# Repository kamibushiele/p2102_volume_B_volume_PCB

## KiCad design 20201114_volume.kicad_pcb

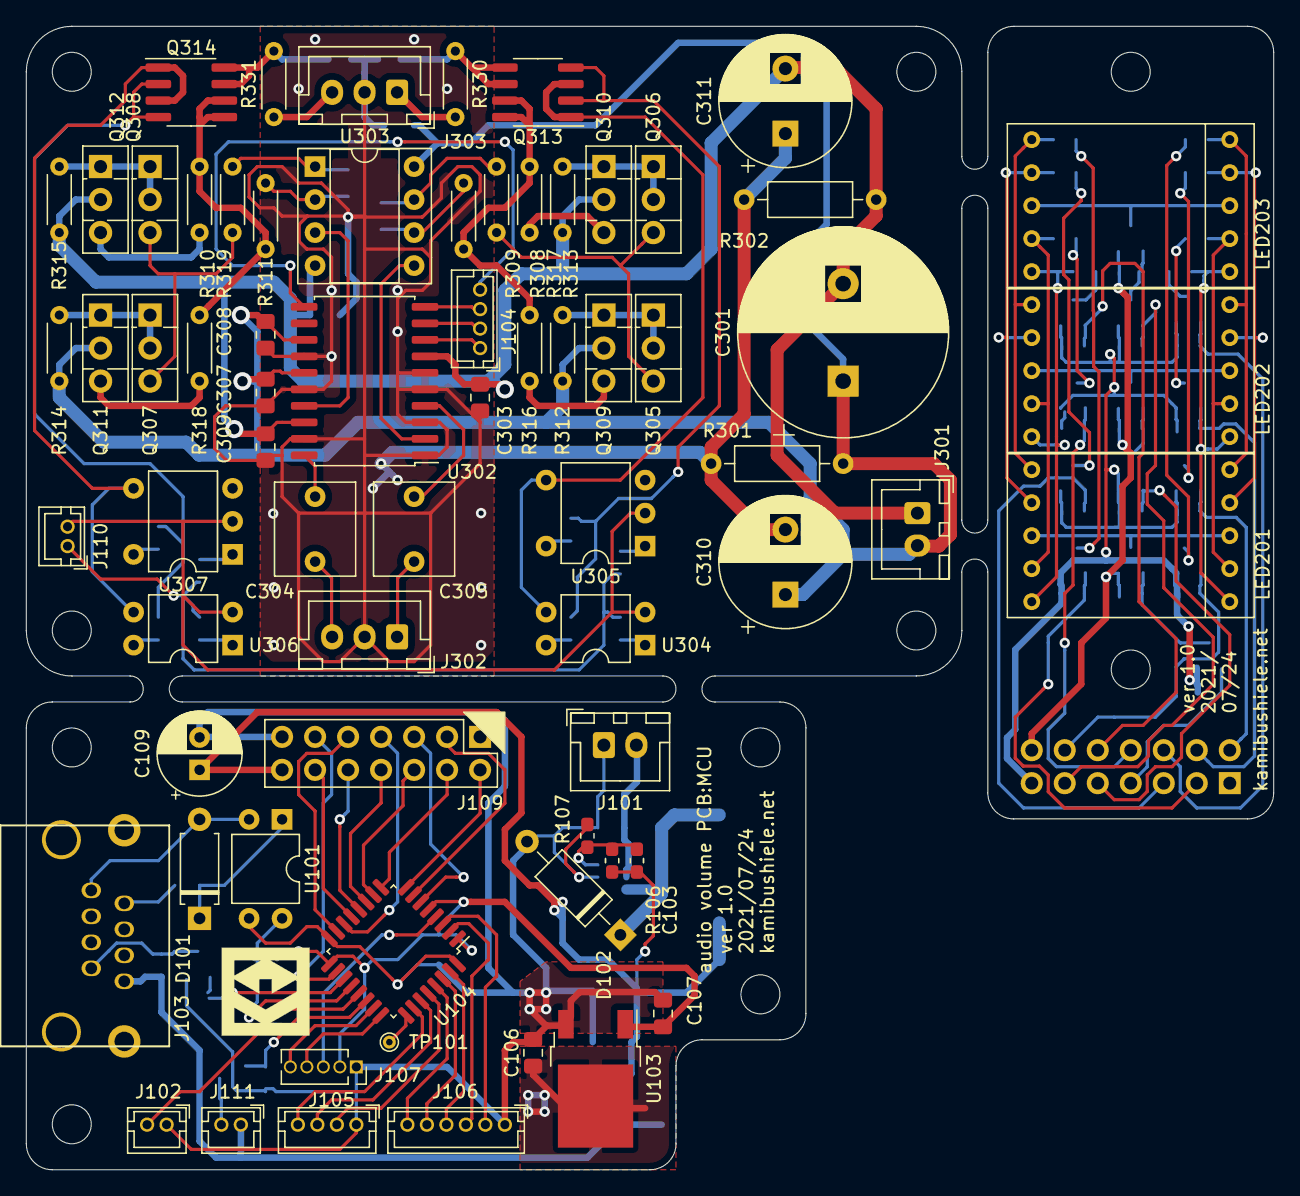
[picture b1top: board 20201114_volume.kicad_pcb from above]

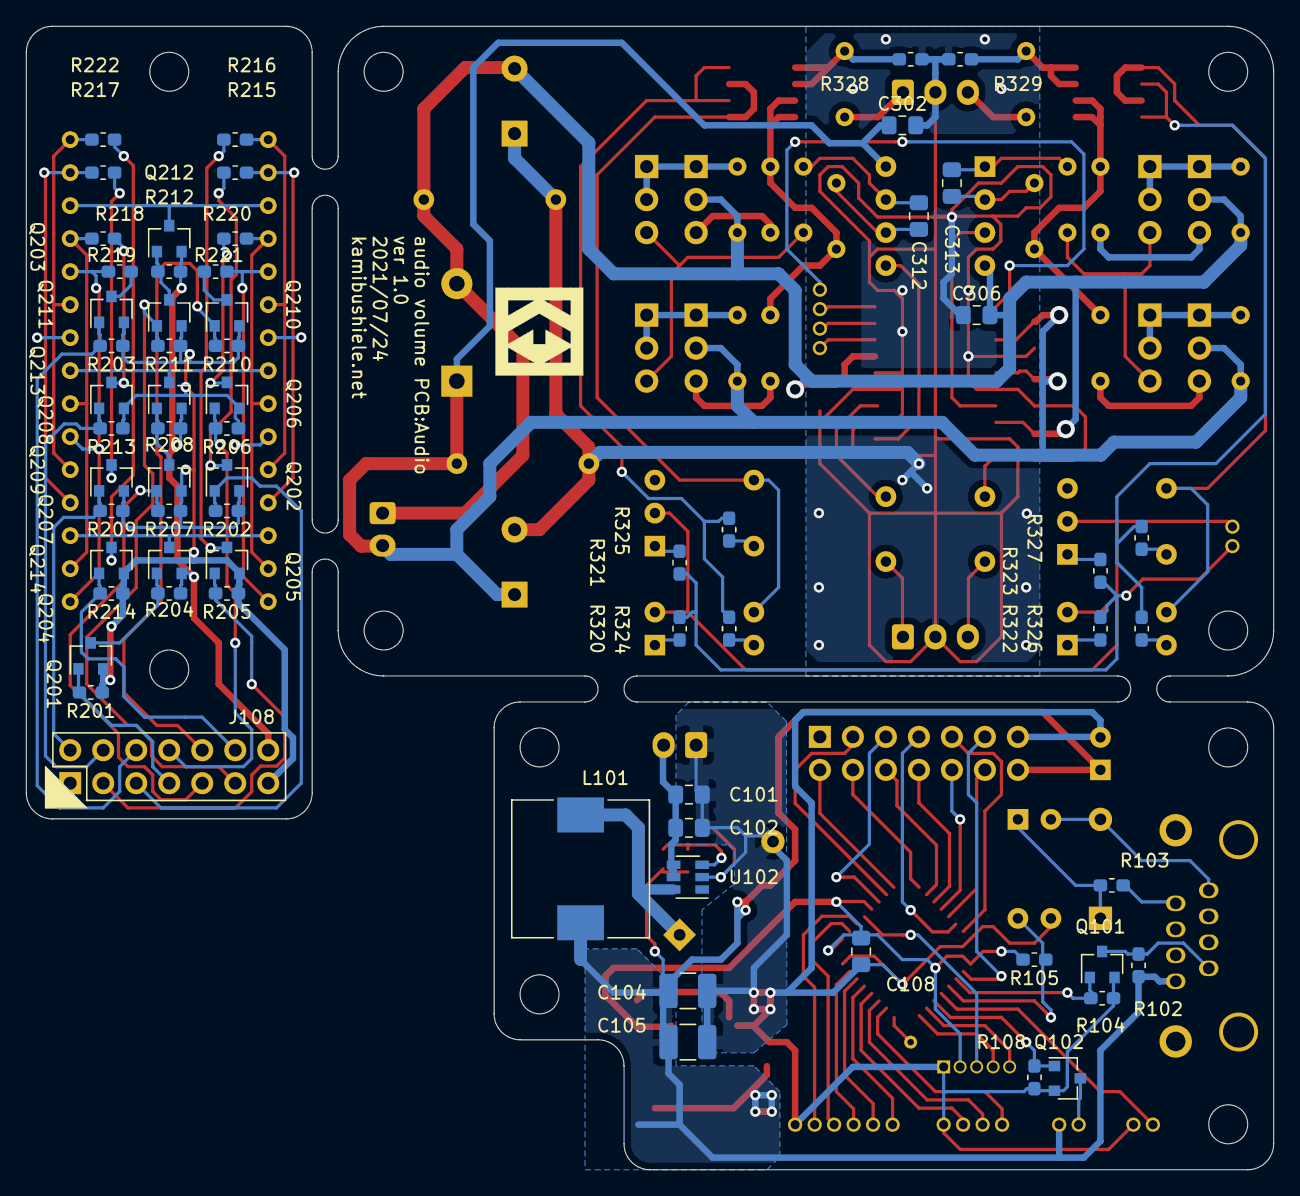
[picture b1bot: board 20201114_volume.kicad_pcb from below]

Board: 2 copper layers, 96.0 x 88.0 mm, 144 parts (65 on the bottom side), 120 nets.

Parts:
C101: 2.2uF 25V; C_0805_2012Metric_Pad1.15x1.40mm_HandSolder
C102: 2.2uF 25V NC; C_0805_2012Metric_Pad1.15x1.40mm_HandSolder
C103: 1000pF 50V; C_0603_1608Metric_Pad1.05x0.95mm_HandSolder
C104: 47uF 16V; C_1210_3225Metric_Pad1.42x2.65mm_HandSolder
C105: 47uF 16V NC; C_1210_3225Metric_Pad1.42x2.65mm_HandSolder
C106, C107, C108, C303, C307, C308, C309: 0.1u; C_0805_2012Metric_Pad1.15x1.40mm_HandSolder
C109: NC 47u; CP_Radial_D6.3mm_P2.50mm
C301: 470u; CP_Radial_D16.0mm_P7.50mm
C302, C306, C312, C313: NC; C_0805_2012Metric_Pad1.15x1.40mm_HandSolder
C304, C305: 1u; C_Rect_L7.0mm_W6.0mm_P5.00mm
C310, C311: 470u; CP_Radial_D10.0mm_P5.00mm
D101: D; D_A-405_P7.62mm_Horizontal
D102: SB240LES; D_A-405_P10.16mm_Horizontal
H101, H102, H103, H104, H201, H202, H301, H302, H303, H304: mounting_hole; M3-drillHole_6mm_nosilk_nopad
J101, J301: POWER; JST_XH_B2B-XH-A_1x02_P2.50mm_Vertical
J102: POWER_SW_DETECT; JST_ZH_B2B-ZR_1x02_P1.50mm_Vertical
J103: 8P8C_Shielded; 7810-8P8C
J104: AudiotoMCU; JST_ZH_B4B-ZR_1x04_P1.50mm_Vertical
J105: MCUtoAudio; JST_ZH_B4B-ZR_1x04_P1.50mm_Vertical
J106: ENC; JST_ZH_B6B-ZR_1x06_P1.50mm_Vertical
J107: SWD; PinSocket_1x05_P1.27mm_Vertical
J108: LEDtoMCU; PinHeader_2x07_P2.54mm_Vertical
J109: MCUtoLED; PinHeader_2x07_P2.54mm_Vertical
J110, J111: Mute; JST_ZH_B2B-ZR_1x02_P1.50mm_Vertical
J302, J303: IN; JST_XH_B3B-XH-A_1x03_P2.50mm_Vertical
L101: 22u; L_10.4x10.4_H4.8
LED201, LED202, LED203: OSL10564-IYG; OSL10564
Q101, Q102, Q201, Q202, Q203, Q205, Q206, Q207, Q209, Q210, Q211, Q213, Q214: 2N7002K; SOT-23
Q204, Q208, Q212: IRLML2246TRPbF; SOT-23
Q305, Q307, Q309, Q311: TTC004B; TO-126-3_Vertical
Q306, Q308, Q310, Q312: TTA004B; TO-126-3_Vertical
Q313, Q314: [mu]PA2753GR; SOP-8_3.76x4.96mm_P1.27mm
R102: 10k_NC; R_0603_1608Metric_Pad1.05x0.95mm_HandSolder
R103, R215, R216, R217, R218, R219, R220, R221, R222, R324, R325, R326, R327: 220; R_0603_1608Metric_Pad1.05x0.95mm_HandSolder
R104, R108, R201, R202, R203, R205, R206, R207, R209, R210, R211, R213, R214: 100k; R_0603_1608Metric_Pad1.05x0.95mm_HandSolder
R105: 100k_NC; R_0603_1608Metric_Pad1.05x0.95mm_HandSolder
R106: 3k; R_0603_1608Metric_Pad1.05x0.95mm_HandSolder
R107, R320, R322: 1k; R_0603_1608Metric_Pad1.05x0.95mm_HandSolder
R204, R208, R212, R328, R329: 10k; R_0603_1608Metric_Pad1.05x0.95mm_HandSolder
R301, R302: 1k; R_Axial_DIN0207_L6.3mm_D2.5mm_P10.16mm_Horizontal
R308, R310, R330, R331: 10; R_Axial_DIN0204_L3.6mm_D1.6mm_P5.08mm_Horizontal
R309, R311: 0; R_Axial_DIN0204_L3.6mm_D1.6mm_P5.08mm_Horizontal
R312, R313, R314, R315: 1.2k; R_Axial_DIN0204_L3.6mm_D1.6mm_P5.08mm_Horizontal
R316, R317, R318, R319: 5; R_Axial_DIN0204_L3.6mm_D1.6mm_P5.08mm_Horizontal
R321, R323: 500; R_0603_1608Metric_Pad1.05x0.95mm_HandSolder
TP101: TestPoint; TestPoint_THTPad_D1.0mm_Drill0.5mm
U101: TLP785; DIP-4_W7.62mm
U102: NJW1933-T; SOT-23-6
U103: NJU7223FDL1-33; TO-252-2
U104: STM32F042K6Tx; LQFP-32_7x7mm_P0.8mm
U302: LM1972; SOIC-20W_7.5x12.8mm_P1.27mm
U303: OPAMP; DIP-8_W7.62mm_Socket
U304, U306: TLP4227G; DIP-4_W7.62mm
U305, U307: TLP591B; DIP-5-6_W7.62mm

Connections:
+3V3: C107.1, C108.1, J107.2, R105.2, U103.1, U104.1, U104.5, U104.17
+5V: C103.1, C104.1, C105.1, C106.1, C109.1, J103.1, J109.14, J111.1, L101.2, R102.1, R106.1, U103.2
+5V_1: J108.14, Q204.2, Q208.2, Q212.2, R204.2, R208.2, R212.2
/5Vsw: D102.1, L101.1, U102.6
/Audio/clk: J104.2, U302.9
/Audio/dat: J104.4, U302.11
/Audio/dgnd: J104.1, U302.8
/Audio/fb1: Q313.7, Q313.8, R309.1, R316.2, R317.1
/Audio/fb2: Q314.5, Q314.6, R311.1, R318.2, R319.1
/Audio/in1: C305.1, U302.4
/Audio/in2: C304.1, U302.20
/Audio/load: J104.3, U302.10
/Audio/mute+: J110.1, R320.2, R321.2, R322.2, R323.2
/Audio/mute-: J110.2, U304.2, U305.2, U306.2, U307.2
/Audio/out1: J303.1, R330.1
/Audio/out2: J303.3, R331.1
/Audio/volout1: U302.2, U303.5
/Audio/volout2: U302.17, U303.3
/BTN_1: J106.6, U104.29
/BTN_2: J106.5, U104.30
/BTN_3: J106.4, U104.31
/ENC_A: J106.3, U104.2
/ENC_B: J106.2, U104.3
/LED: TP101.1, U104.25
/NRST: J107.3, U104.4
/SEG_LED_A_1: J109.7, U104.14
/SEG_LED_A_2: J109.9, U104.15
/SEG_LED_A_3: J109.11, U104.18
/SEG_LED_K_A: J109.5, U104.6
/SEG_LED_K_B: J109.3, U104.7
/SEG_LED_K_C: J109.2, U104.8
/SEG_LED_K_D: J109.4, U104.9
/SEG_LED_K_DP: J109.12, U104.13
/SEG_LED_K_E: J109.6, U104.10
/SEG_LED_K_F: J109.8, U104.11
/SEG_LED_K_G: J109.10, U104.12
/SWCLK: J107.4, U104.24
/SWDIO: J107.5, U104.23
/display/1: LED201.3, LED201.8, Q204.3
/display/2: LED202.3, LED202.8, Q208.3
/display/3: LED203.3, LED203.8, Q212.3
/display/A_COM1: J108.7, Q201.1, R201.2
/display/A_COM2: J108.9, Q207.1, R207.2
/display/A_COM3: J108.11, Q211.1, R211.2
/display/K_A: J108.5, Q202.1, R202.2
/display/K_B: J108.3, Q205.1, R205.2
/display/K_C: J108.2, Q209.1, R209.2
/display/K_D: J108.4, Q213.1, R213.2
/display/K_DP: J108.12, Q214.1, R214.2
/display/K_E: J108.6, Q203.1, R203.2
/display/K_F: J108.8, Q206.1, R206.2
/display/K_G: J108.10, Q210.1, R210.2
/display/a: Q202.3, R215.2
/display/b: Q205.3, R216.2
/display/c: Q209.3, R217.2
/display/d: Q213.3, R218.2
/display/dp: Q214.3, R222.2
/display/e: Q203.3, R219.2
/display/f: Q206.3, R220.2
/display/g: Q210.3, R221.2
/ext_MISO: R105.1, U101.4, U104.20
/ext_MOSI: Q101.1, R104.2, U104.19
/mute: Q102.1, R108.2, U104.22
/power_sw: J102.2, U104.21
/vol_clk: J105.2, U104.28
/vol_dat: J105.4, U104.26
/vol_load: J105.3, U104.27
GND: C101.2, C102.2, C104.2, C105.2, C106.2, C107.2, C108.2, C109.2, D102.2, J101.1, J102.1, J105.1, J106.1, J107.1, J109.13, Q101.2, Q102.2, R104.1, R107.2, R108.1, U101.3, U102.2, U103.3, U104.16, U104.32
GNDA: C302.2, C303.2, C306.1, C307.1, C308.2, C309.2, C310.2, C311.1, J302.2, J303.2, R301.2, R302.1, R328.1, R329.1, U302.1, U302.3, U302.5, U302.6, U302.14, U302.16, U302.19
GND_1: J108.13, Q201.2, Q202.2, Q203.2, Q205.2, Q206.2, Q207.2, Q209.2, Q210.2, Q211.2, Q213.2, Q214.2, R201.1, R202.1, R203.1, R205.1, R206.1, R207.1, R209.1, R210.1, R211.1, R213.1, R214.1
unnamed: C103.2, R106.2, R107.1, U102.3
unnamed: C304.2, J302.3
unnamed: C305.2, J302.1
unnamed: C312.1, R308.2, U303.7
unnamed: C312.2, R309.2, U303.6
unnamed: C313.1, R310.2, U303.1
unnamed: C313.2, R311.2, U303.2
unnamed: D101.1, R103.1, U101.1
unnamed: D101.2, J103.8, U101.2
unnamed: J103.2, Q101.3, R102.2
unnamed: J103.7, R103.2
unnamed: J111.2, Q102.3
unnamed: LED201.1, LED202.1, LED203.1, R219.1
unnamed: LED201.2, LED202.2, LED203.2, R218.1
unnamed: LED201.4, LED202.4, LED203.4, R217.1
unnamed: LED201.5, LED202.5, LED203.5, R222.1
unnamed: LED201.6, LED202.6, LED203.6, R216.1
unnamed: LED201.7, LED202.7, LED203.7, R215.1
unnamed: LED201.9, LED202.9, LED203.9, R220.1
unnamed: LED201.10, LED202.10, LED203.10, R221.1
unnamed: Q201.3, Q204.1, R204.1
unnamed: Q207.3, Q208.1, R208.1
unnamed: Q211.3, Q212.1, R212.1
unnamed: Q305.1, Q305.2, Q309.1, R312.2
unnamed: Q305.3, Q306.3, R308.1
unnamed: Q306.1, Q306.2, Q310.1, R313.1
unnamed: Q307.1, Q307.2, Q311.1, R314.2
unnamed: Q307.3, Q308.3, R310.1
unnamed: Q308.1, Q308.2, Q312.1, R315.1
unnamed: Q309.3, R316.1
unnamed: Q310.3, R317.2
unnamed: Q311.3, R318.1
unnamed: Q312.3, R319.2
unnamed: Q313.1, Q313.3, U304.3, U305.4
unnamed: Q313.2, Q313.4, R324.1, R325.1
unnamed: Q313.5, Q313.6, R328.2, R330.2
unnamed: Q314.1, Q314.3, U306.3, U307.4
unnamed: Q314.2, Q314.4, R326.1, R327.1
unnamed: Q314.7, Q314.8, R329.2, R331.2
unnamed: R320.1, U304.1
unnamed: R321.1, U305.1
unnamed: R322.1, U306.1
unnamed: R323.1, U307.1
unnamed: R324.2, U304.4
unnamed: R325.2, U305.6
unnamed: R326.2, U306.4
unnamed: R327.2, U307.6
VCC: C101.1, C102.1, J101.2, U102.4, U102.5
VDDA: C301.1, C302.1, C307.2, C308.1, C310.1, J301.2, Q309.2, Q311.2, R301.1, R312.1, R314.1, U302.13, U302.15, U303.8
VSSA: C301.2, C303.1, C306.2, C309.1, C311.2, J301.1, Q310.2, Q312.2, R302.2, R313.2, R315.2, U302.7, U302.18, U303.4

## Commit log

2021-08-29 v1.0
